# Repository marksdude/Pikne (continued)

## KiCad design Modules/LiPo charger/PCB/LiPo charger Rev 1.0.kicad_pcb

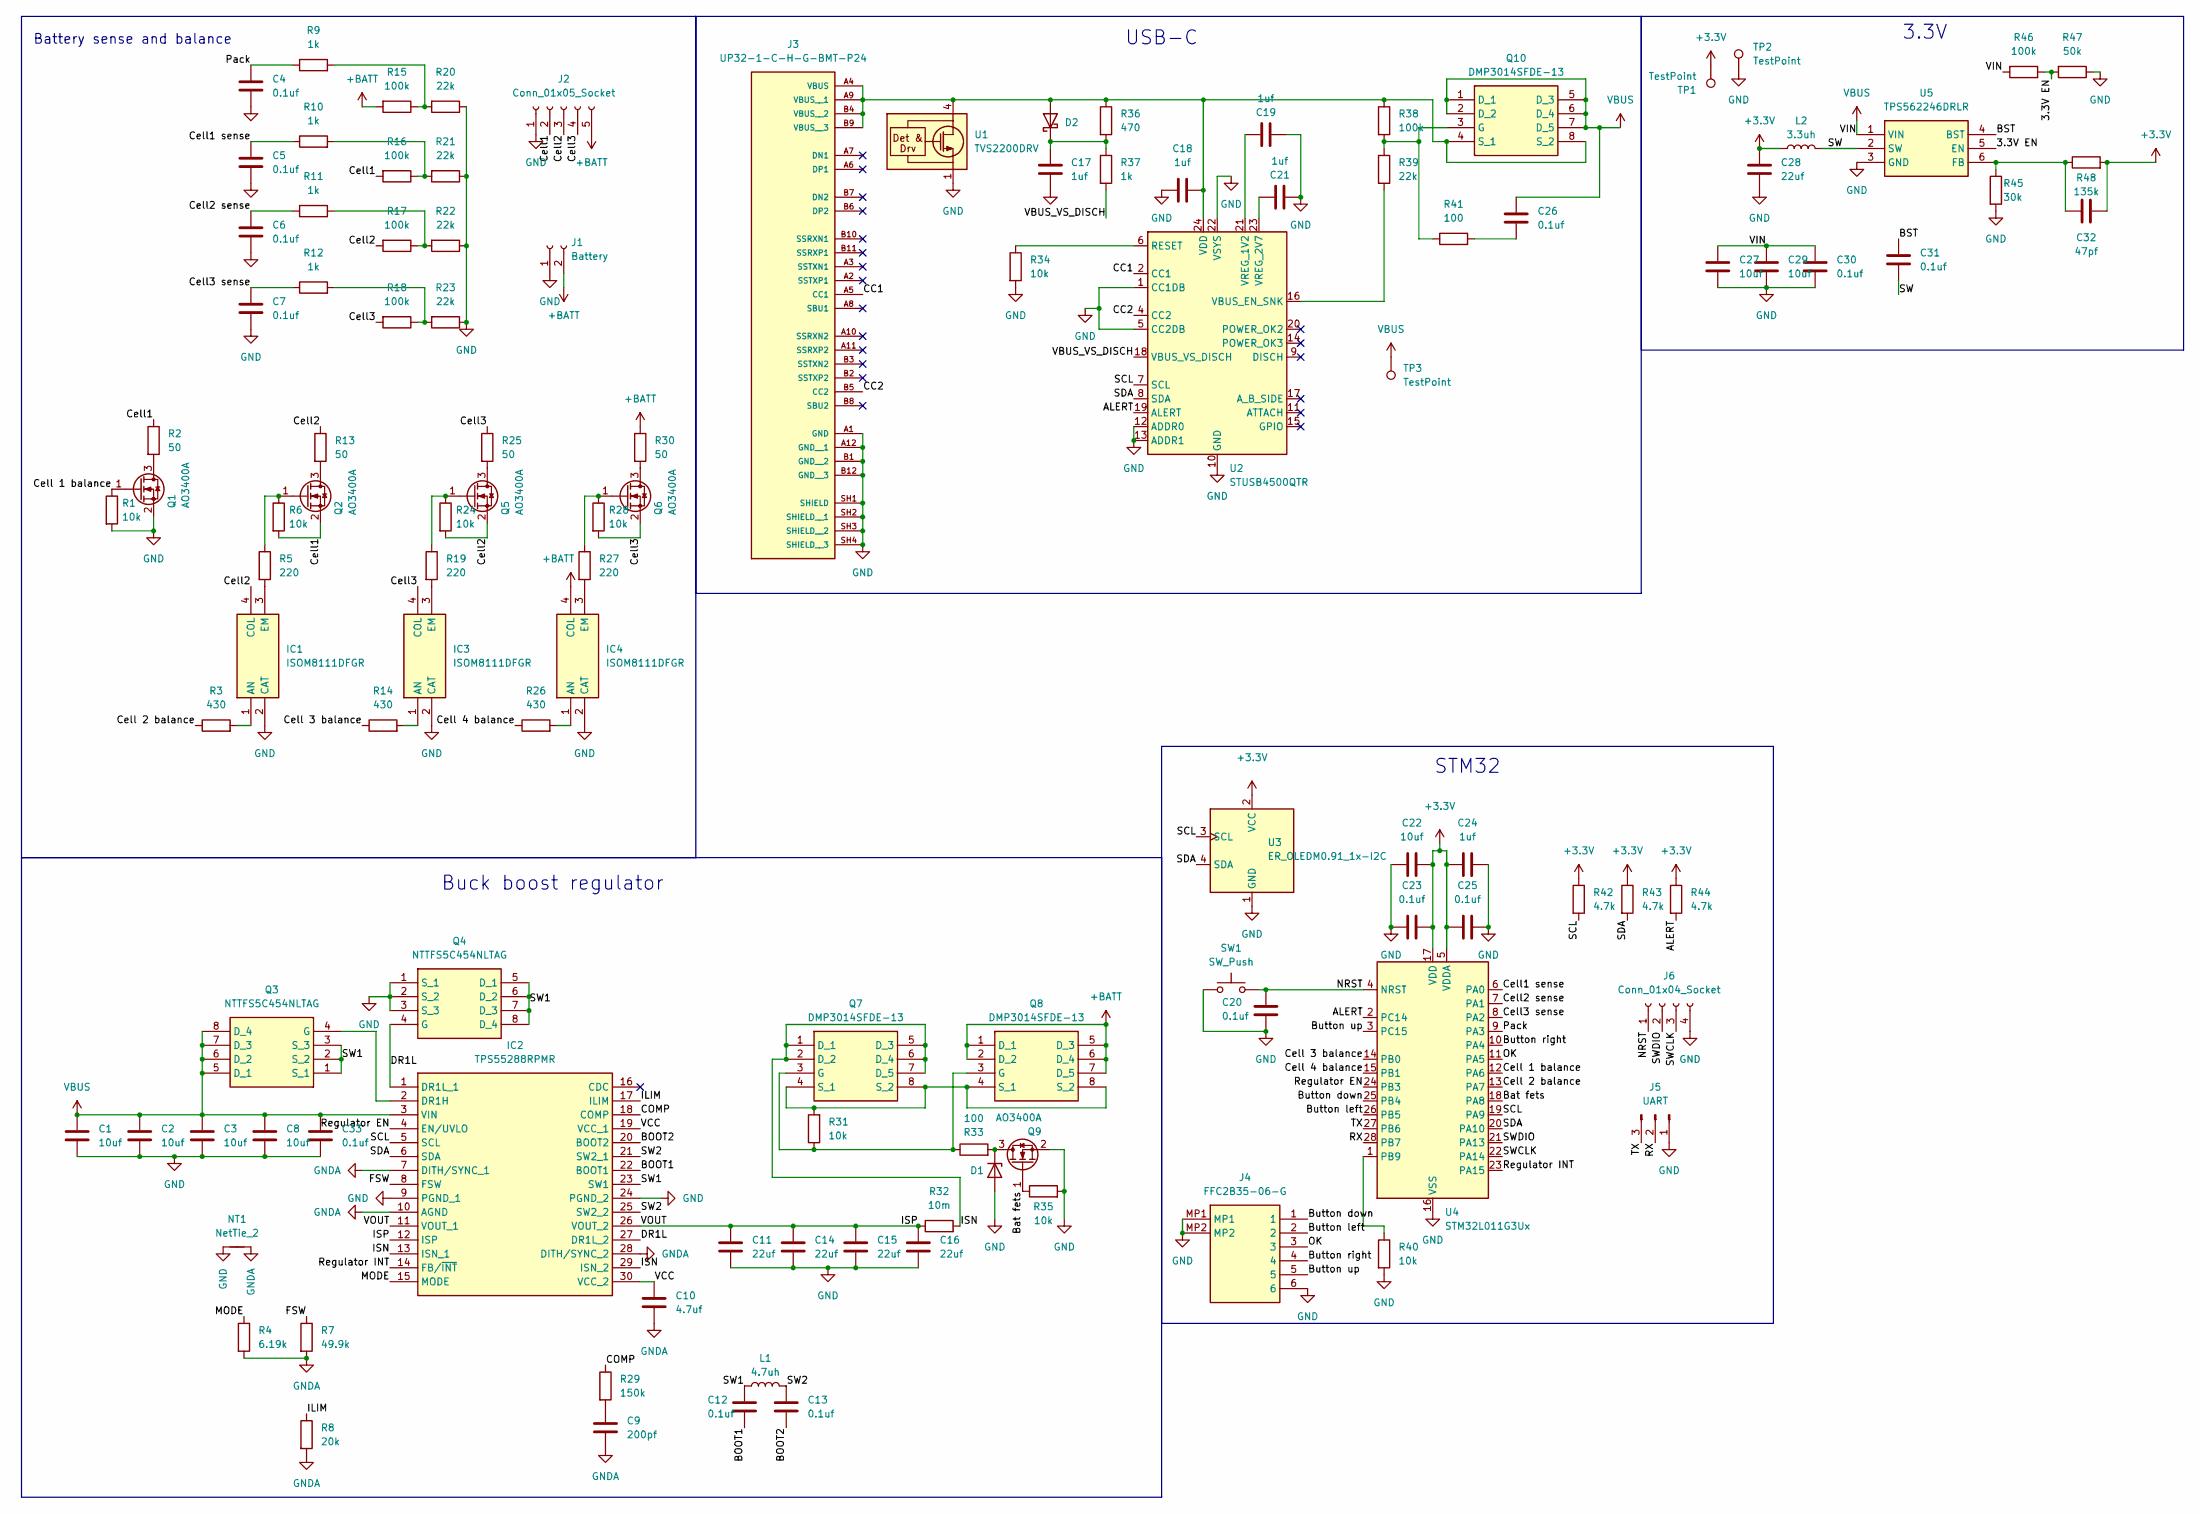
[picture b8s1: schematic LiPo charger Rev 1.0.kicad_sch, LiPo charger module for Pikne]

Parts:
C1, C2, C3, C8: 10uf; C_1206_3216Metric
C4, C5, C6, C7, C12, C13, C20, C23, C26, C30, C31, C33: 0.1uf; C_0402_1005Metric
C9: 200pf; C_0402_1005Metric
C10: 4.7uf; C_0603_1608Metric
C11, C14, C15, C16: 22uf; C_1206_3216Metric
C17, C18, C24: 1uf; C_0603_1608Metric
C19, C21: 1uf; C_0402_1005Metric
C22, C27, C29: 10uf; C_0603_1608Metric
C25: 0.1uf; R_0402_1005Metric
C28: 22uf; C_0805_2012Metric
C32: 47pf; C_0201_0603Metric
D1: D_Zener; D_SOD-323_HandSoldering
D2: D_Schottky; D_SOD-323_HandSoldering
IC1, IC3, IC4: ISOM8111DFGR; SOP254P700X240-4N; Manufacturer_Part_Number ISOM8111DFGR
IC2: TPS55288RPMR; Mouser Part Number 595-TPS55288RPMR
J1: Battery; JST_VH_B2P-VH-B_1x02_P3.96mm_Vertical
J2: Conn_01x05_Socket; JST_XH_S5B-XH-A_1x05_P2.50mm_Horizontal
J3: UP32-1-C-H-G-BMT-P24; SAMESKY_UP32-1-C-H-G-BMT-P24; PARTREV 1.0
J4: FFC2B35-06-G; FFC2B3506G; Mouser Part Number 640-FFC2B35-06-G
J5: UART; JST_ZH_B3B-ZR_1x03_P1.50mm_Vertical
J6: Conn_01x04_Socket; JST_ZH_B4B-ZR_1x04_P1.50mm_Vertical
L1: 4.7uh; L_Bourns_SRP1038C_10.0x10.0mm
L2: 3.3uh; INDC3225X120N
NT1: NetTie_2; NetTie-2_SMD_Pad0.5mm
Q1, Q2, Q5, Q6, Q9: AO3400A; SOT-23
Q3, Q4: NTTFS5C454NLTAG; WDFN8_3.3X3.3_0.65P_CASE_511AB_ISSUE_D_1; Mouser Part Number 863-NTTFS5C454NLTAG
Q7, Q8, Q10: DMP3014SFDE-13; DMP1022UFDEQ7; Manufacturer_Part_Number DMP3014SFDE-13
R1, R6, R24, R28, R40: 10k; R_0402_1005Metric
R2, R13, R25, R30: 50; R_0603_1608Metric
R3, R14, R26: 430; R_0603_1608Metric
R4: 6.19k; R_0603_1608Metric
R5, R19, R27: 220; R_0603_1608Metric
R7: 49.9k; R_0402_1005Metric
R8: 20k; R_0603_1608Metric
R9, R10, R11, R12: 1k; R_0402_1005Metric
R15, R16, R17, R18, R38: 100k; R_0603_1608Metric
R20, R21, R22, R23: 22k; R_0402_1005Metric
R29: 150k; R_0402_1005Metric
R31, R34, R35: 10k; R_0603_1608Metric
R32: 10m; R_1206_3216Metric
R33: 100; R_0603_1608Metric
R36: 470; R_0402_1005Metric
R37: 1k; R_0603_1608Metric
R39: 22k; R_0603_1608Metric
R41: 100; R_0402_1005Metric
R42, R43, R44: 4.7k; R_0603_1608Metric
R45: 30k; R_0402_1005Metric
R46: 100k; R_0402_1005Metric
R47: 50k; R_0402_1005Metric
R48: 135k; R_0402_1005Metric
SW1: SW_Push; SW_SPST_B3U-1000P
TP1, TP2, TP3: TestPoint; TestPoint_Pad_D1.0mm
U1: TVS2200DRV; WSON-6-1EP_2x2mm_P0.65mm_EP1x1.6mm
U2: STUSB4500QTR; QFN-24-1EP_4x4mm_P0.5mm_EP2.7x2.7mm
U3: ER_OLEDM0.91_1x-I2C
U4: STM32L011G3Ux; QFN-28_4x4mm_P0.5mm
U5: TPS562246DRLR; SOTFL50P160X60-6N; Mouser Part Number 595-TPS562246DRLR

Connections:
+3.3V: C22.2, C23.2, C24.1, C25.1, C28.1, C32.1, L2.1, R42.1, R43.1, R44.1, R48.2, TP1.1 (1_1), U3.2 (VCC), U4.5 (VDDA), U4.17 (VDD)
+BATT: IC4.4 (COL), J1.2, J2.5, Q8.1 (D_1), Q8.2 (D_2), Q8.5 (D_3), Q8.6 (D_4), Q8.7 (D_5), R15.2, R30.1
/3.3V EN: R46.1, R47.2, U5.5 (EN)
/ALERT: R44.2, U2.19 (ALERT), U4.2 (PC14)
/BOOT1: C12.2, IC2.22 (BOOT1)
/BOOT2: C13.2, IC2.20 (BOOT2)
/BST: C31.2, U5.4 (BST)
/Bat fets: Q9.1 (G), R35.1, U4.18 (PA8)
/Button down: J4.1, U4.25 (PB4)
/Button left: J4.2, U4.26 (PB5)
/Button right: J4.4, U4.10 (PA4)
/Button up: J4.5, U4.3 (PC15)
/CC1: J3.A5 (CC1), U2.2 (CC1)
/CC2: J3.B5 (CC2), U2.4 (CC2)
/COMP: IC2.18 (COMP), R29.1
/Cell1: J2.2, Q2.2 (S), R2.1, R6.2, R16.2
/Cell1 sense: C5.1, R10.1, U4.6 (PA0)
/Cell2: IC1.4 (COL), J2.3, Q5.2 (S), R13.1, R17.2, R24.2
/Cell2 sense: C6.1, R11.1, U4.7 (PA1)
/Cell3: IC3.4 (COL), J2.4, Q6.2 (S), R18.2, R25.1, R28.2
/Cell3 sense: C7.1, R12.1, U4.8 (PA2)
/Cell 1 balance: Q1.1 (G), R1.1, U4.12 (PA6)
/Cell 2 balance: R3.1, U4.13 (PA7)
/Cell 3 balance: R14.1, U4.14 (PB0)
/Cell 4 balance: R26.1, U4.15 (PB1)
/DR1L: IC2.1 (DR1L_1), IC2.27 (DR1L_2), Q4.4 (G)
/FSW: IC2.8 (FSW), R7.1
/ILIM: IC2.17 (ILIM), R8.1
/ISN: IC2.13 (ISN_1), IC2.29 (ISN_2), Q7.1 (D_1), Q7.2 (D_2), Q7.5 (D_3), Q7.6 (D_4), Q7.7 (D_5), R32.2
/ISP: C11.1, C14.1, C15.1, C16.1, IC2.11 (VOUT_1), IC2.12 (ISP), IC2.26 (VOUT_2), R32.1
/MODE: IC2.15 (MODE), R4.1
/NRST: C20.2, J6.1, SW1.2, U4.4 (NRST)
/OK: J4.3, U4.11 (PA5)
/Pack: C4.1, R9.1, U4.9 (PA3)
/RX: J5.2, U4.28 (PB7)
/Regulator EN: IC2.4 (EN/UVLO), U4.24 (PB3)
/Regulator INT: IC2.14 (FB/~INT), U4.23 (PA15)
/SCL: IC2.5 (SCL), R42.2, U2.7 (SCL), U3.3 (SCL), U4.19 (PA9)
/SDA: IC2.6 (SDA), R43.2, U2.8 (SDA), U3.4 (SDA), U4.20 (PA10)
/SW: C31.1, L2.2, U5.2 (SW)
/SW1: C12.1, IC2.23 (SW1), L1.1, Q3.1 (S_1), Q3.2 (S_2), Q3.3 (S_3), Q4.5 (D_1), Q4.6 (D_2), Q4.7 (D_3), Q4.8 (D_4), Q4.9, Q4.10, Q4.11
/SW2: C13.1, IC2.21 (SW2_1), IC2.25 (SW2_2), L1.2
/SWCLK: J6.3, U4.22 (PA14)
/SWDIO: J6.2, U4.21 (PA13)
/TX: J5.3, U4.27 (PB6)
/VBUS_VS_DISCH: R37.2, U2.18 (VBUS_VS_DISCH)
/VCC: C10.1, IC2.19 (VCC_1), IC2.30 (VCC_2)
GND: C1.2, C2.2, C3.2, C4.2, C5.2, C6.2, C7.2, C8.2, C11.2, C14.2, C15.2, C16.2, C17.1, C18.1, C19.1, C20.1, C21.1, C22.1, C23.1, C24.2, C25.2, C27.2, C28.2, C29.2, C30.2, C33.2, D1.2 (A), IC1.2 (CAT), IC2.9 (PGND_1), IC2.24 (PGND_2), IC3.2 (CAT), IC4.2 (CAT), J1.1, J2.1, J3.A1 (GND), J3.A12 (GND__1), J3.B1 (GND__2), J3.B12 (GND__3), J3.SH1 (SHIELD), J3.SH2 (SHIELD__1), J3.SH3 (SHIELD__2), J3.SH4 (SHIELD__3), J4.6, J4.MP1, J4.MP2, J5.1, J6.4, NT1.1, Q1.2 (S), Q4.1 (S_1), Q4.2 (S_2), Q4.3 (S_3), Q9.2 (S), R1.2, R20.1, R21.1, R22.1, R23.1, R34.2, R35.2, R40.2, R45.2, R47.1, SW1.1, TP2.1 (1_1), U1.1 (GND), U1.2 (GND), U1.3 (GND), U1.7 (GND), U2.1 (CC1DB), U2.5 (CC2DB), U2.10 (GND), U2.12 (ADDR0), U2.13 (ADDR1), U2.22 (VSYS), U2.25 (GND), U3.1 (GND), U4.16 (VSS), U5.3 (GND)
GNDA: C9.2, C10.2, IC2.7 (DITH/SYNC_1), IC2.10 (AGND), IC2.28 (DITH/SYNC_2), NT1.2, R4.2, R7.2, R8.2
unnamed: C9.1, R29.2
unnamed: C26.2, R41.2
unnamed: D1.1 (K), Q9.3 (D), R33.2
unnamed: C18.2, D2.2 (A), J3.A4 (VBUS), J3.A9 (VBUS__1), J3.B4 (VBUS__2), J3.B9 (VBUS__3), Q10.4 (S_1), Q10.8 (S_2), R36.1, R38.1, U1.4 (IN), U1.5 (IN), U1.6 (IN), U2.24 (VDD)
unnamed: C17.2, D2.1 (K), R36.2, R37.1
unnamed: IC1.1 (AN), R3.2
unnamed: IC1.3 (EM), R5.2
unnamed: IC2.2 (DR1H), Q3.4 (G)
unnamed: IC3.1 (AN), R14.2
unnamed: IC3.3 (EM), R19.2
unnamed: IC4.1 (AN), R26.2
unnamed: IC4.3 (EM), R27.2
unnamed: Q1.3 (D), R2.2
unnamed: Q2.3 (D), R13.2
unnamed: Q2.1 (G), R5.1, R6.1
unnamed: Q5.3 (D), R25.2
unnamed: Q5.1 (G), R19.1, R24.1
unnamed: Q6.3 (D), R30.2
unnamed: Q6.1 (G), R27.1, R28.1
unnamed: Q7.3 (G), Q8.3 (G), R31.1, R33.1
unnamed: Q7.4 (S_1), Q7.8 (S_2), Q8.4 (S_1), Q8.8 (S_2), R31.2
unnamed: Q10.3 (G), R38.2, R39.1, R41.1
unnamed: R10.2, R16.1, R21.2
unnamed: R11.2, R17.1, R22.2
unnamed: R12.2, R18.1, R23.2
unnamed: R9.2, R15.1, R20.2
unnamed: R34.1, U2.6 (RESET)
unnamed: R39.2, U2.16 (VBUS_EN_SNK)
unnamed: C19.2, U2.21 (VREG_1V2)
unnamed: C21.2, U2.23 (VREG_2V7)
unnamed: R40.1, U4.1 (PB9)
unnamed: C32.2, R45.1, R48.1, U5.6 (FB)
VBUS: C1.1, C2.1, C3.1, C8.1, C26.1, C27.1, C29.1, C30.1, C33.1, IC2.3 (VIN), Q3.5 (D_1), Q3.6 (D_2), Q3.7 (D_3), Q3.8 (D_4), Q3.9, Q3.10, Q3.11, Q10.1 (D_1), Q10.2 (D_2), Q10.5 (D_3), Q10.6 (D_4), Q10.7 (D_5), R46.2, TP3.1 (1_1), U5.1 (VIN)

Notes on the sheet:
Buck boost regulator
3.3V
Battery sense and balance
USB-C
STM32

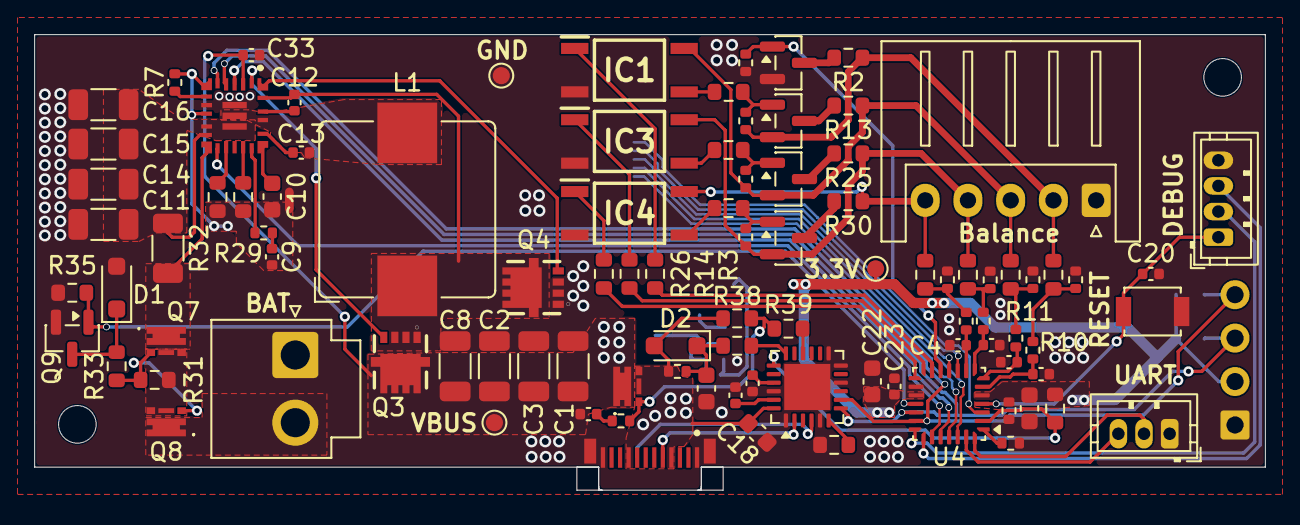
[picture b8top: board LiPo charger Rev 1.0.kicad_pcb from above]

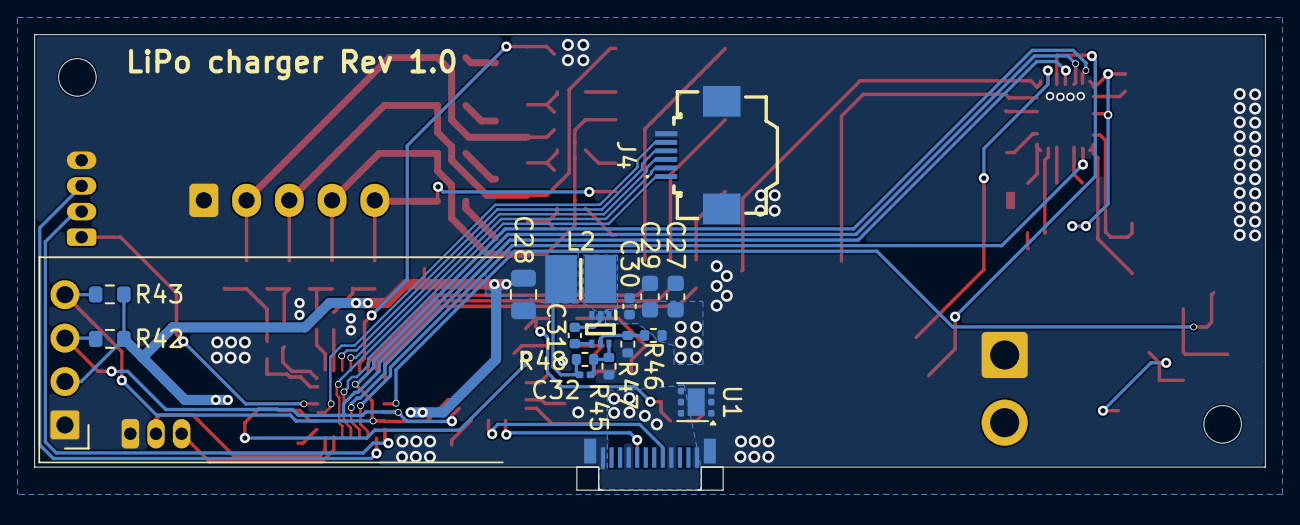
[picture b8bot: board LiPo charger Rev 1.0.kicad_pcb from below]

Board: 2 copper layers, 72.0 x 26.7 mm, 115 parts (17 on the bottom side), 82 nets.

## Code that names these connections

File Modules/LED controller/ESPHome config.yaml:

esphome:
  name: led-controller
  friendly_name: LED controller

esp32:
  board: esp32-c3-devkitm-1
  framework:
    type: esp-idf

# Enable logging
logger:

# Enable Home Assistant API
api:
  encryption:
    key:  # add a key here

ota:
  - platform: esphome

wifi:
  ssid: !secret wifi_ssid
  password: !secret wifi_password

  ap:
    ssid: "Led-Controller"
    password:  # add a password here

captive_portal:

output:
- platform: ledc
  id: output_ledc_1
  pin: GPIO4
- platform: ledc
  id: output_ledc_2
  pin: GPIO5
- platform: ledc
  id: output_ledc_3
  pin: GPIO7

light:
  - platform: esp32_rmt_led_strip
    channel_colors: GRB
    pin: GPIO3
    num_leds: 50
    chipset: ws2812
    name: "Addressable LED"
    effects: 
      - addressable_flicker:
      - addressable_fireworks:
      - addressable_random_twinkle:
      - addressable_twinkle: 
      - addressable_scan:
      - addressable_color_wipe:
      - addressable_rainbow:
      - flicker:

# Choose either monochrome or RGB
  - platform: rgb
    name: RGB Light
    id: light_rgb_1
    blue: output_ledc_1
    green: output_ledc_2
    red: output_ledc_3
    
  - platform: monochromatic
    name: Monochromatic Light 1
    id: light_monochromatic_1
    output: output_ledc_1
  - platform: monochromatic
    name: Monochromatic Light 2
    id: light_monochromatic_2
    output: output_ledc_2




event:
  - platform: uart
    id: Ready
    event_types:
      - "Ready" : [0x00]
    on_event:
      then:
        - uart.write: [0x01]

uart:
  baud_rate: 115200
  rx_pin: GPIO20
  tx_pin: GPIO21
  debug:
    direction: RX
    dummy_receiver: true
    after:
      delimiter: \n
    sequence:
      - lambda: |-
          std::string data = "";
          float bat;
          float current;
          float usb_current;
          float voltage;
          for(uint8_t byte : bytes){
            data += byte;
          }
          size_t bat_algus = data.find("Bat:");
          if(bat_algus != std::string::npos){
            bat_algus += 4;
            size_t bat_lopp = data.find("|", bat_algus);
            bat = stof(data.substr(bat_algus, bat_lopp - bat_algus));
          }
          size_t current_algus = data.find("Current:");
          if(current_algus != std::string::npos){
            current_algus += 8;
            size_t current_lopp = data.find("|", current_algus);
            current = stof(data.substr(current_algus, current_lopp - current_algus));
          }
          size_t voltage_algus = data.find("Voltage:");
          if(voltage_algus != std::string::npos){
            voltage_algus += 8;
            size_t voltage_lopp = data.find("|", voltage_algus);
            voltage = stof(data.substr(voltage_algus, voltage_lopp - voltage_algus));
          }
          size_t usb_current_algus = data.find("USB_current:");
          if(usb_current_algus != std::string::npos){
            usb_current_algus += 12;
            size_t usb_current_lopp = data.find("|", usb_current_algus);
            usb_current = stof(data.substr(usb_current_algus, usb_current_lopp - usb_current_algus));
          }
          id(bat_charge).publish_state(bat);
          id(bat_current).publish_state(current);
          id(bat_voltage).publish_state(voltage);
          id(USB_current).publish_state(usb_current);
          
          
      





sensor:
  - platform: template
    name: Battery
    id: bat_charge
    device_class: battery
    unit_of_measurement: "%"
  - platform: template
    name: battery current
    id: bat_current
    device_class: current
    unit_of_measurement: A
    accuracy_decimals: 1
  - platform: template
    name: Battery voltage
    id: bat_voltage
    device_class: voltage
    unit_of_measurement: V
    accuracy_decimals: 1
  - platform: template
    name: USB current
    id: USB_current
    accuracy_decimals: 1
    device_class: current
    unit_of_measurement: A
  
